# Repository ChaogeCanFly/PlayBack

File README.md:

# Augmented reality System - Playback
The study of bats requires the ability to record and generate sound waves in the ultrasonic ranges. The required bandwidth for such systems is up to 100kHz, which is much higher than the common acoustic systems designed for humans. Studying bat echolocation capabilities and generating real time acoustic responses requires a minimal latency acoustic system. The few available systems on the market aren`t designed for real time signal processing and manipulation. In order to meet those constrains, a full acoustic system was developed. The system includes a Smart microphone module embedded with a microprocessor, a Speaker-amplifier and a Switch box which is capable of signal redirection and real time processing.

## PlayBack
The PlayBack setup consists of three main modules: Smart Microphones, a Switch and speaker amplifiers.  It is designed to monitor audio signals from multiple microphone modules and direct a signal from a selected microphone to an array of speaker modules including DSP options for audio processing in real time. The setup is designed to work at an audio bandwidth of 1-100 kHz at up to 1MS/S.
 
 ### 3d Models:
The casings for the modules have been designed in Fusion 360 and 3d printed
[Microphone](https://a360.co/2HDuYLZ)
[Switch](https://a360.co/36yYfSj)
[Amplifier](https://a360.co/2WX1Lmh)

### System Diagram
The system’s topology is such that the microphone modules are connected to the switch module using a standard RJ25 cable. The 6 wires of the cable are used to pass the following between the Smart microphones and the Switch: power to the module, trigger signal, the audio signal and an analog “quality” signal. The Switch module consists of two MCU`s (Micro Controller Unit), one is used as the Switch interface, and routes the signals while the other is used as a DSP MCU to implement signal processing in real time to the acoustic signal. The speaker amplifiers are connected through an RJ45 cable which in turn is used to supply power from the switch to the amplifiers and transmit the audio signals and the enable signal to the amplifier. The Switch module is connected to a Matlab GUI application running on a PC using an Xbee adapter for wireless operation. In addition, a Saleae logic analyzer is connected to the Switch allowing to monitor the analog signals and the trigger signal.

### Smart Microphone
The Smart microphone module is designed to meet the required acoustic bandwidth of bat echolocation calls. In addition, since the system requirements are minimal latency for signal processing and signal manipulation, each of the microphones are embedded with a dedicated microprocessor which is responsible for the initial signal processing of the individual acoustic source. Such an approach allows spreading the computational power required by the system and simplifies the decision-making requirements of the Switch by reducing the acoustic information to a more simplified representation of an acoustic source. i.e. digital triggers / signal quality indication. This approach also allows future expending of the system since each of the microphones acts as an independent entity responsible for its own acoustic system. Adding more microphone to a system will not influence the required signal processing for the main unit.

### Switch
The Switch Module is used as the center piece of the system. It connects all the Smart microphone modules and Speaker amplifiers, has an analog routing circuitry to route one of the microphone signals to several speakers. In addition, it acts as a power delivery system, converting a single supply source to several voltage levels for the various components of the system. The switch contains several status indicators such as active speaker LEDs, external trigger. Connectors for all the analog signals running through the system and generally configured status LEDs for future configurations. The switch module contains two MCUs, Switch MCU and DSP MCU, the Switch MCU is used as the system interface and responsible for routing the acoustic signals and monitor the trigger events from the Smart Microphones, while the DSP MCU is used as a DSP and implements various signal processing algorithms.

### Speaker amplifier
Generating sounds in the ultrasonic frequencies (above 20kHz) requires a dedicated amplifier. Since commercial amplifiers are usually designed for the human hearing range and are commonly implemented through power efficient amplifiers (Class D). These speakers work as digital switches at high frequencies above the human hearing thresholds. The high frequency digital switching is converted to an analog signal using the natural low pass filtering characteristics of the speaker coils. The attempt to use such an amplifier at an ultrasonic frequency will result in high frequency distortions if any sound is generated at all since the common amplifiers are implemented with filters to cut the ultrasonic ranges from the input signals.

### GUI Microphone
To control the software parameters of the Smart Microphone, a GUI was created in Matlab. The Microphone has a UART communication over USB with the PC through the MCU`s micro USB connection or through an Xbee adapter board connected to its mate at the PC - as a wireless configuration. The GUI is designed with several section, Connection settings section, Parameters setting and display section, Messages section and Microphone updates section.

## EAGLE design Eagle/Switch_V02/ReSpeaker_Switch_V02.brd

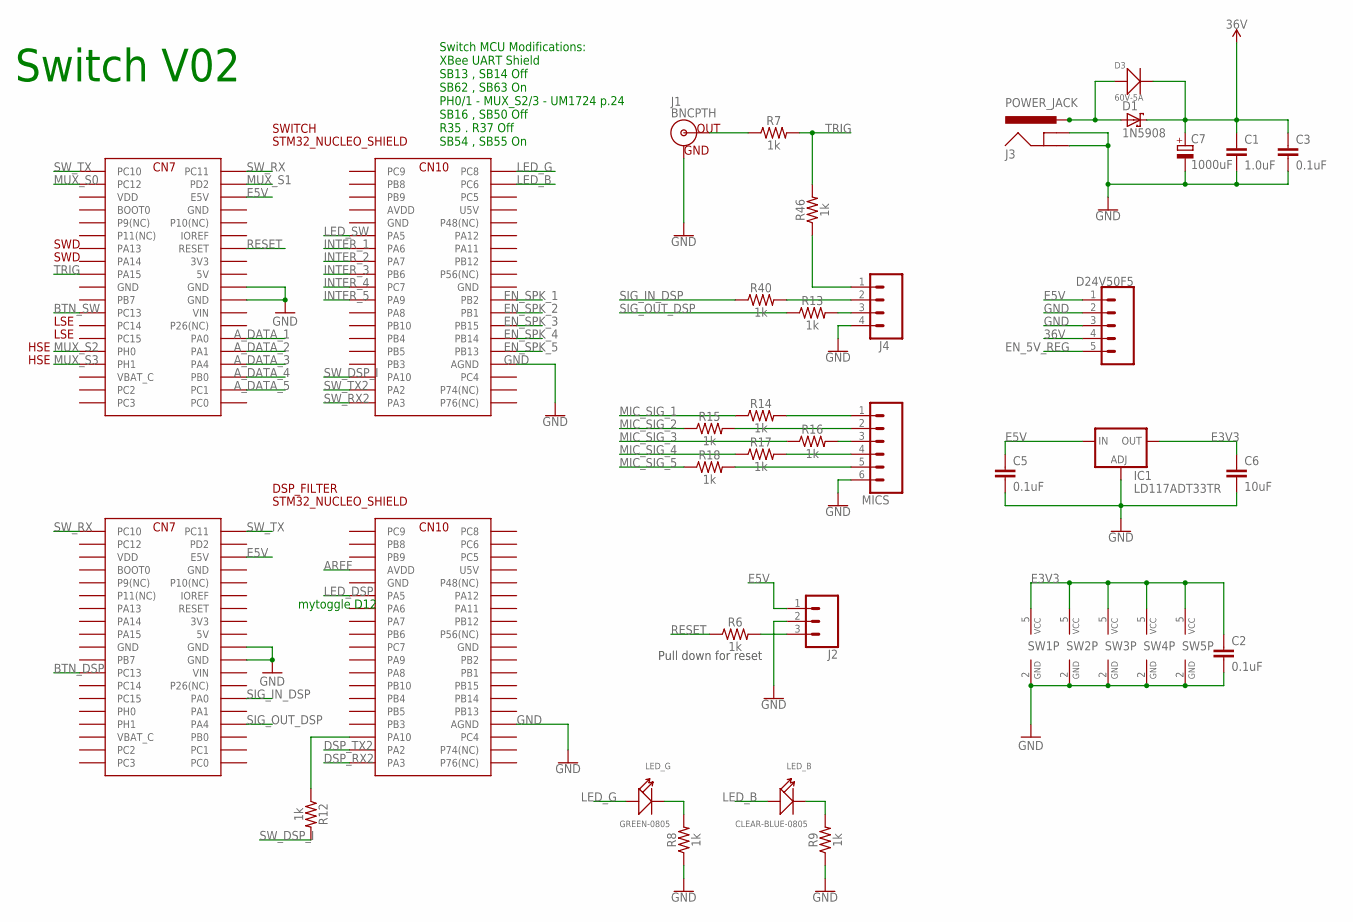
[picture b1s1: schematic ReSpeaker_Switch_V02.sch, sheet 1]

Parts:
C1: 1.0uF; 0805
C2, C3, C5: 0.1uF; 0805
C6: 10uF; 0805
C7: 1000uF; E7,5-16
D1: 1N5908; C4111-15
D3: 60V-5A; DO-214AB
D24V50F5: CONN_05; 1X05
DSP_FILTER: STM32_NUCLEO_SHIELD; STM32_NUCLEO
IC1: LD117ADT33TR; DPACK
J1: BNCPTH; BNC
J2: CONN_03POLAR; MOLEX-1X3
J3: POWER_JACK; POWER_JACK_PTH
J4: CONN_04POLAR; MOLEX-1X4
LED_B: CLEAR-BLUE-0805; LED-0805
LED_G: GREEN-0805; LED-0805
MICS: CONN_06POLAR; MOLEX-1X6
R6, R7, R8, R9, R12, R13, R14, R15, R16, R17, R18, R40, R46: 1k; 0805
SW1, SW2, SW3, SW4, SW5: 741G3157DBVR; DBV_R-PDSO-G6
SWITCH: STM32_NUCLEO_SHIELD; STM32_NUCLEO

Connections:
3V3: DSP_FILTER.3V3, SWITCH.3V3
5V: DSP_FILTER.5V, SWITCH.5V
36V: C1.1, C3.1, C7.+, D1.C, D3.2 (-), D24V50F5.4; also elsewhere on the board
AREF: DSP_FILTER.AVDD
AVDD: SWITCH.AVDD
A_DATA_1: SWITCH.PA0; also elsewhere on the board
A_DATA_2: SWITCH.PA1; also elsewhere on the board
A_DATA_3: SWITCH.PA4; also elsewhere on the board
A_DATA_4: SWITCH.PB0; also elsewhere on the board
A_DATA_5: SWITCH.PC1; also elsewhere on the board
BTN_DSP: DSP_FILTER.PC13
BTN_SW: SWITCH.PC13
DSP_RX2: DSP_FILTER.PA3
DSP_TX2: DSP_FILTER.PA2
E3V3: C2.1, C6.1, IC1.4 (OUT), SW1.5 (VCC), SW2.5 (VCC), SW3.5 (VCC), SW4.5 (VCC), SW5.5 (VCC); also elsewhere on the board
E5V: C5.1, D24V50F5.1, DSP_FILTER.E5V, IC1.3 (IN), J2.1, SWITCH.E5V; also elsewhere on the board
EN_5V_REG: D24V50F5.5
EN_SPK_1: SWITCH.PB2; also elsewhere on the board
EN_SPK_2: SWITCH.PB1; also elsewhere on the board
EN_SPK_3: SWITCH.PB15; also elsewhere on the board
EN_SPK_4: SWITCH.PB14; also elsewhere on the board
EN_SPK_5: SWITCH.PB13; also elsewhere on the board
GND: C1.2, C2.2, C3.2, C5.2, C6.2, C7.-, D24V50F5.2, D24V50F5.3, DSP_FILTER.AGND, DSP_FILTER.GND@8 (GND), DSP_FILTER.GND@19 (GND), DSP_FILTER.GND@20 (GND), DSP_FILTER.GND@22 (GND), DSP_FILTER.GND@47 (GND), DSP_FILTER.GND@58 (GND), IC1.1 (ADJ), J1.GND, J2.2, J3.GND, J3.GNDBREAK, J4.4, MICS.6, R8.1, R9.1, SW1.2 (GND), SW2.2 (GND), SW3.2 (GND), SW4.2 (GND), SW5.2 (GND), SWITCH.AGND, SWITCH.GND@8 (GND), SWITCH.GND@19 (GND), SWITCH.GND@20 (GND), SWITCH.GND@22 (GND), SWITCH.GND@47 (GND), SWITCH.GND@58 (GND); also elsewhere on the board
INTER_1: SWITCH.PA6; also elsewhere on the board
INTER_2: SWITCH.PA7; also elsewhere on the board
INTER_3: SWITCH.PB6; also elsewhere on the board
INTER_4: SWITCH.PC7; also elsewhere on the board
INTER_5: SWITCH.PA9; also elsewhere on the board
LED_B: LED_B.+, SWITCH.PC6
LED_DSP: DSP_FILTER.PA5
LED_G: LED_G.+, SWITCH.PC8
LED_SW: SWITCH.PA5
MIC_SIG_1: R14.1; also elsewhere on the board
MIC_SIG_2: R15.1; also elsewhere on the board
MIC_SIG_3: R16.1; also elsewhere on the board
MIC_SIG_4: R17.1; also elsewhere on the board
MIC_SIG_5: R18.1; also elsewhere on the board
MUX_S0: SWITCH.PC12; also elsewhere on the board
MUX_S1: SWITCH.PD2; also elsewhere on the board
MUX_S2: SWITCH.PH0; also elsewhere on the board
MUX_S3: SWITCH.PH1; also elsewhere on the board
unnamed: DSP_FILTER.PA10, R12.1
unnamed: D1.A, D3.1 (+), J3.PWR
unnamed: J1.S (OUT), R7.1
unnamed: J2.3, R6.2
unnamed: MICS.1, R14.2
unnamed: LED_G.-, R8.2
unnamed: LED_B.-, R9.2
unnamed: MICS.2, R15.2
unnamed: MICS.3, R16.2
unnamed: MICS.4, R17.2
unnamed: MICS.5, R18.2
unnamed: J4.2, R40.2
unnamed: J4.3, R13.2
unnamed: J4.1, R46.1
RESET: R6.1, SWITCH.RESET
SIG_IN_DSP: DSP_FILTER.PA0, R40.1; also elsewhere on the board
SIG_OUT_DSP: DSP_FILTER.PA4, R13.1; also elsewhere on the board
SW_DSP_I: R12.2, SWITCH.PA10
SW_RX: DSP_FILTER.PC10, SWITCH.PC11
SW_RX2: SWITCH.PA3
SW_TX: DSP_FILTER.PC11, SWITCH.PC10
SW_TX2: SWITCH.PA2
TRIG: R7.2, R46.2, SWITCH.PA15
U5V: DSP_FILTER.U5V, SWITCH.U5V
VBAT_C: DSP_FILTER.VBAT_C, SWITCH.VBAT_C
VDD: DSP_FILTER.VDD, SWITCH.VDD
VIN: DSP_FILTER.VIN, SWITCH.VIN

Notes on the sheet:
SWD
LSE
Switch V02
Pull down for reset
Switch MCU Modifications: XBee UART Shield SB13 , SB14 Off SB62 , SB63 On PH0/1 - MUX_S2/3 - UM1724 p.24 SB16 , SB50 Off R35 . R37 Off SB54 , SB55 On
HSE
mytoggle D12

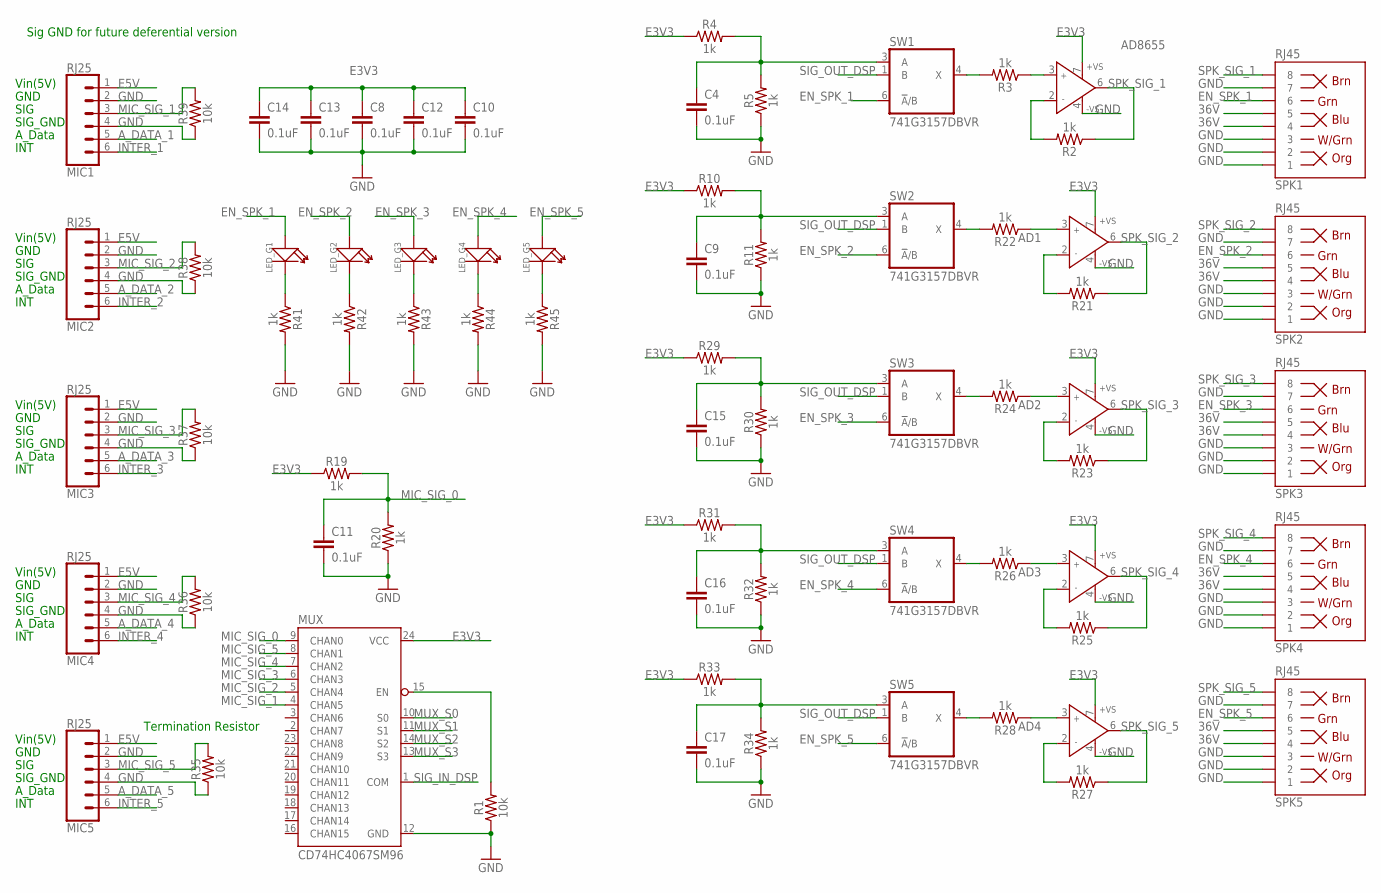
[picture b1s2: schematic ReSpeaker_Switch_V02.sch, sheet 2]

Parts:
AD1, AD2, AD3, AD4, AD8655: AD8655R; SO8
C4, C8, C9, C10, C11, C12, C13, C14, C15, C16, C17: 0.1uF; 0805
LED_G1, LED_G2, LED_G3, LED_G4, LED_G5: GREEN-0805; LED-0805
MIC1, MIC2, MIC3, MIC4, MIC5: RJ25; RJ11-6
MUX: CD74HC4067SM96; SSOP24
R1, R35, R36, R37, R38, R39: 10k; 0805
R2, R3, R4, R5, R10, R11, R19, R20, R21, R22, R23, R24, R25, R26, R27, R28, R29, R30, R31, R32, R33, R34, R41, R42, R43, R44, R45: 1k; 0805
SPK1, SPK2, SPK3, SPK4, SPK5: RJ45; RJ45-8
SW1, SW2, SW3, SW4, SW5: 741G3157DBVR; DBV_R-PDSO-G6

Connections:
36V: SPK1.4, SPK1.5, SPK2.4, SPK2.5, SPK3.4, SPK3.5, SPK4.4, SPK4.5, SPK5.4, SPK5.5; also elsewhere on the board
A_DATA_1: MIC1.5; also elsewhere on the board
A_DATA_2: MIC2.5; also elsewhere on the board
A_DATA_3: MIC3.5; also elsewhere on the board
A_DATA_4: MIC4.5; also elsewhere on the board
A_DATA_5: MIC5.5; also elsewhere on the board
E3V3: AD1.7 (+VS), AD2.7 (+VS), AD3.7 (+VS), AD4.7 (+VS), AD8655.7 (+VS), C8.1, C10.1, C12.1, C13.1, C14.1, MUX.24 (VCC), R4.1, R10.1, R19.1, R29.1, R31.1, R33.1; also elsewhere on the board
E5V: MIC1.1, MIC2.1, MIC3.1, MIC4.1, MIC5.1; also elsewhere on the board
EN_MUX: MUX.15 (EN), R1.2
EN_SPK_1: LED_G1.+, SPK1.6, SW1.6 (!A!/B); also elsewhere on the board
EN_SPK_2: LED_G2.+, SPK2.6, SW2.6 (!A!/B); also elsewhere on the board
EN_SPK_3: LED_G3.+, SPK3.6, SW3.6 (!A!/B); also elsewhere on the board
EN_SPK_4: LED_G4.+, SPK4.6, SW4.6 (!A!/B); also elsewhere on the board
EN_SPK_5: LED_G5.+, SPK5.6, SW5.6 (!A!/B); also elsewhere on the board
GND: AD1.4 (-VS), AD2.4 (-VS), AD3.4 (-VS), AD4.4 (-VS), AD8655.4 (-VS), C4.2, C8.2, C9.2, C10.2, C11.2, C12.2, C13.2, C14.2, C15.2, C16.2, C17.2, MIC1.2, MIC1.4, MIC2.2, MIC2.4, MIC3.2, MIC3.4, MIC4.2, MIC4.4, MIC5.2, MIC5.4, MUX.12 (GND), R1.1, R5.1, R11.1, R20.1, R30.1, R32.1, R34.1, R35.1, R36.1, R37.1, R38.1, R39.1, R41.2, R42.2, R43.2, R44.2, R45.2, SPK1.1, SPK1.2, SPK1.3, SPK1.7, SPK2.1, SPK2.2, SPK2.3, SPK2.7, SPK3.1, SPK3.2, SPK3.3, SPK3.7, SPK4.1, SPK4.2, SPK4.3, SPK4.7, SPK5.1, SPK5.2, SPK5.3, SPK5.7; also elsewhere on the board
INTER_1: MIC1.6; also elsewhere on the board
INTER_2: MIC2.6; also elsewhere on the board
INTER_3: MIC3.6; also elsewhere on the board
INTER_4: MIC4.6; also elsewhere on the board
INTER_5: MIC5.6; also elsewhere on the board
MIC_SIG_0: C11.1, MUX.9 (CHAN0), R19.2, R20.2
MIC_SIG_1: MIC1.3, MUX.4 (CHAN5), R39.2; also elsewhere on the board
MIC_SIG_2: MIC2.3, MUX.5 (CHAN4), R38.2; also elsewhere on the board
MIC_SIG_3: MIC3.3, MUX.6 (CHAN3), R37.2; also elsewhere on the board
MIC_SIG_4: MIC4.3, MUX.7 (CHAN2), R36.2; also elsewhere on the board
MIC_SIG_5: MIC5.3, MUX.8 (CHAN1), R35.2; also elsewhere on the board
MUX_S0: MUX.10 (S0); also elsewhere on the board
MUX_S1: MUX.11 (S1); also elsewhere on the board
MUX_S2: MUX.14 (S2); also elsewhere on the board
MUX_S3: MUX.13 (S3); also elsewhere on the board
unnamed: R3.2, SW1.4 (X)
unnamed: AD8655.3 (IN+), R3.1
unnamed: AD8655.2 (IN-), R2.2
unnamed: C4.1, R4.2, R5.2, SW1.3 (A)
unnamed: C9.1, R10.2, R11.2, SW2.3 (A)
unnamed: AD1.2 (IN-), R21.2
unnamed: AD2.2 (IN-), R23.2
unnamed: AD1.3 (IN+), R22.1
unnamed: AD2.3 (IN+), R24.1
unnamed: AD3.2 (IN-), R25.2
unnamed: AD3.3 (IN+), R26.1
unnamed: AD4.2 (IN-), R27.2
unnamed: AD4.3 (IN+), R28.1
unnamed: C15.1, R29.2, R30.2, SW3.3 (A)
unnamed: R22.2, SW2.4 (X)
unnamed: C16.1, R31.2, R32.2, SW4.3 (A)
unnamed: R24.2, SW3.4 (X)
unnamed: C17.1, R33.2, R34.2, SW5.3 (A)
unnamed: R26.2, SW4.4 (X)
unnamed: R28.2, SW5.4 (X)
unnamed: LED_G1.-, R41.1
unnamed: LED_G2.-, R42.1
unnamed: LED_G3.-, R43.1
unnamed: LED_G4.-, R44.1
unnamed: LED_G5.-, R45.1
SIG_IN_DSP: MUX.1 (COM); also elsewhere on the board
SIG_OUT_DSP: SW1.1 (B), SW2.1 (B), SW3.1 (B), SW4.1 (B), SW5.1 (B); also elsewhere on the board
SPK_SIG_1: AD8655.6 (OUT), R2.1, SPK1.8
SPK_SIG_2: AD1.6 (OUT), R21.1, SPK2.8
SPK_SIG_3: AD2.6 (OUT), R23.1, SPK3.8
SPK_SIG_4: AD3.6 (OUT), R25.1, SPK4.8
SPK_SIG_5: AD4.6 (OUT), R27.1, SPK5.8

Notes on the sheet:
SIG
SIG_GND
Vin(5V)
GND
A_Data
INT
Sig GND for future deferential version
Termination Resistor

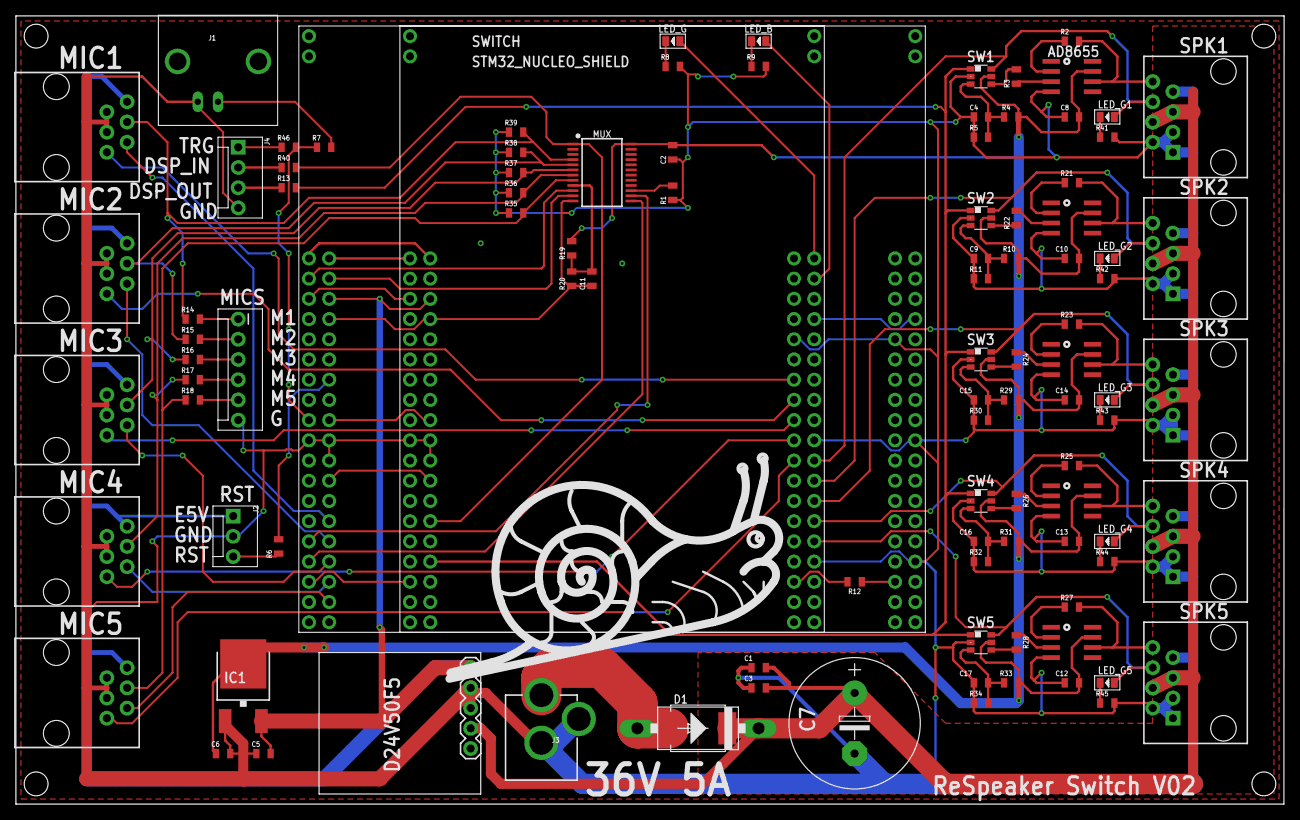
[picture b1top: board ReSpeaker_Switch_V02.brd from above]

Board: 2 copper layers, 159.4 x 99.1 mm, 102 parts (0 on the bottom side), 89 nets.

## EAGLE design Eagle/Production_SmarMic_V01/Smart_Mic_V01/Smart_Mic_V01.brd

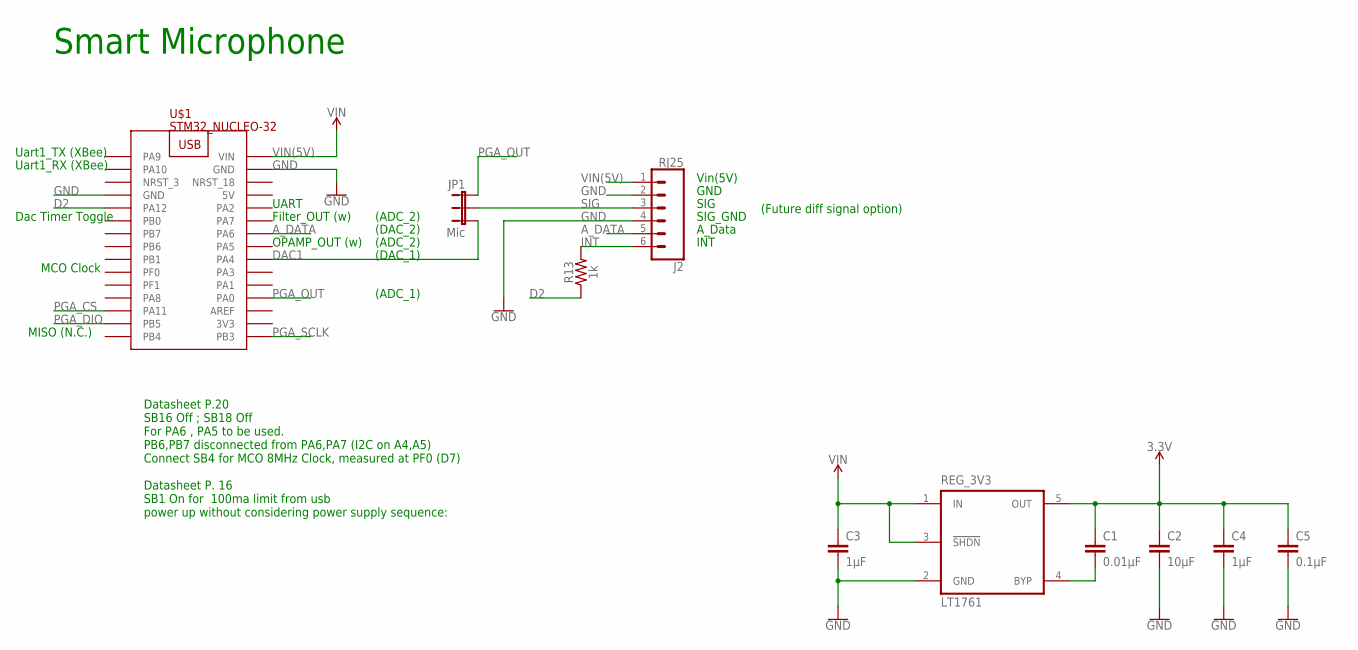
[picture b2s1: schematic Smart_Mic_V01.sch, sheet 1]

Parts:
C1: 0.01µF; 0805
C2: 10µF; 0805
C3, C4: 1µF; 0805
C5: 0.1µF; 0805
J2: RJ25; RJ11-6
JP1: Mic; 1X03
R13: 1k; 0805
REG_3V3: LT1761; SOT23-5
U$1: STM32_NUCLEO-32

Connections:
3.3V: C1.1, C2.1, C4.1, C5.1, REG_3V3.5 (OUT); also elsewhere on the board
3V3: U$1.3V3
5V: U$1.5V
A_DATA: J2.5, U$1.PA6
BYP: C1.2, REG_3V3.4 (BYP)
D2: R13.1, U$1.PA12
DAC1: JP1.3, U$1.PA4
GND: C2.2, C3.2, C4.2, C5.2, J2.2, J2.4, REG_3V3.2 (GND), U$1.GND@4 (GND), U$1.GND@17 (GND); also elsewhere on the board
INT: J2.6, R13.2
PGA_CS: U$1.PA11; also elsewhere on the board
PGA_DIO: U$1.PB5; also elsewhere on the board
PGA_OUT: JP1.1, U$1.PA0; also elsewhere on the board
PGA_SCLK: U$1.PB3; also elsewhere on the board
SIG: J2.3, JP1.2
VIN(5V): C3.1, J2.1, REG_3V3.1 (IN), REG_3V3.3 (!SHDN!), U$1.VIN

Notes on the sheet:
Smart Microphone
SIG
SIG_GND
Vin(5V)
GND
A_Data
INT
(Future diff signal option)
(ADC_1)
(ADC_2)
(DAC_1)
(DAC_2)
UART
Datasheet P.20 SB16 Off ; SB18 Off For PA6 , PA5 to be used. PB6,PB7 disconnected from PA6,PA7 (I2C on A4,A5) Connect SB4 for MCO 8MHz Clock, measured at PF0 (D7) Datasheet P. 16 SB1 On for 100ma limit from usb power up without considering power supply sequence:
MISO (N.C.)
OPAMP_OUT (w)
Filter_OUT (w)
Uart1_TX (XBee)
Uart1_RX (XBee)
MCO Clock
Dac Timer Toggle

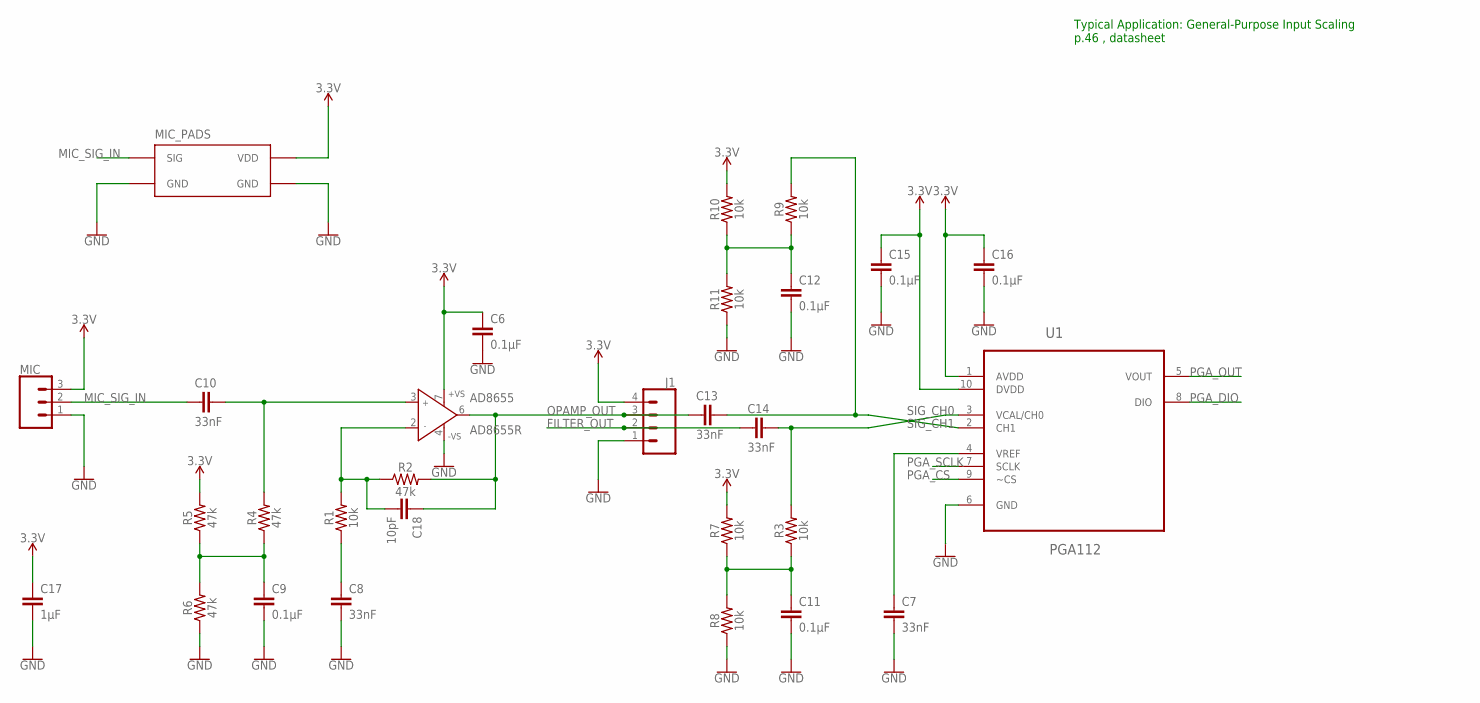
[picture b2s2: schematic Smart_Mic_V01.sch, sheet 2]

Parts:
AD8655: AD8655R; SO8
C6, C9, C11, C12, C15, C16: 0.1µF; 0805
C7, C8, C10, C13, C14: 33nF; 0805
C17: 1µF; 0805
C18: 10pF; 0805
J1: CONN_04; 1X04
MIC: CONN_03; 1X03
R1, R3, R7, R8, R9, R10, R11: 10k; 0805
R2, R4, R5, R6: 47k; 0805
U1: PGA112; SOP50P490X110-10N
U$2: MIC_PADS

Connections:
3.3V: AD8655.7 (+VS), C6.1, C15.1, C16.1, C17.1, J1.4, MIC.3, R5.2, R7.2, R10.2, U1.1 (AVDD), U1.10 (DVDD), U$2.VDD; also elsewhere on the board
FILTER_OUT: C14.2, J1.2
GND: AD8655.4 (-VS), C6.2, C7.2, C8.2, C9.2, C11.2, C12.2, C15.2, C16.2, C17.2, J1.1, MIC.1, R6.1, R8.1, R11.1, U1.6 (GND), U$2.GND$2 (GND), U$2.GND$4 (GND); also elsewhere on the board
MIC_SIG_IN: C10.2, MIC.2, U$2.SIG
unnamed: C7.1, U1.4 (VREF)
unnamed: C9.1, R4.1, R5.1, R6.2
unnamed: C11.1, R3.1, R7.1, R8.2
unnamed: C12.1, R9.1, R10.1, R11.2
unnamed: C8.1, R1.1
OP1_+: AD8655.3 (IN+), C10.1, R4.2
OP1_-: AD8655.2 (IN-), C18.2, R1.2, R2.1
OPAMP_OUT: AD8655.6 (OUT), C13.2, C18.1, J1.3, R2.2
PGA_CS: U1.9 (~CS); also elsewhere on the board
PGA_DIO: U1.8 (DIO); also elsewhere on the board
PGA_OUT: U1.5 (VOUT); also elsewhere on the board
PGA_SCLK: U1.7 (SCLK); also elsewhere on the board
SIG_CH0: C13.1, R9.2, U1.2 (CH1)
SIG_CH1: C14.1, R3.2, U1.3 (VCAL/CH0)

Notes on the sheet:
Typical Application: General-Purpose Input Scaling p.46 , datasheet

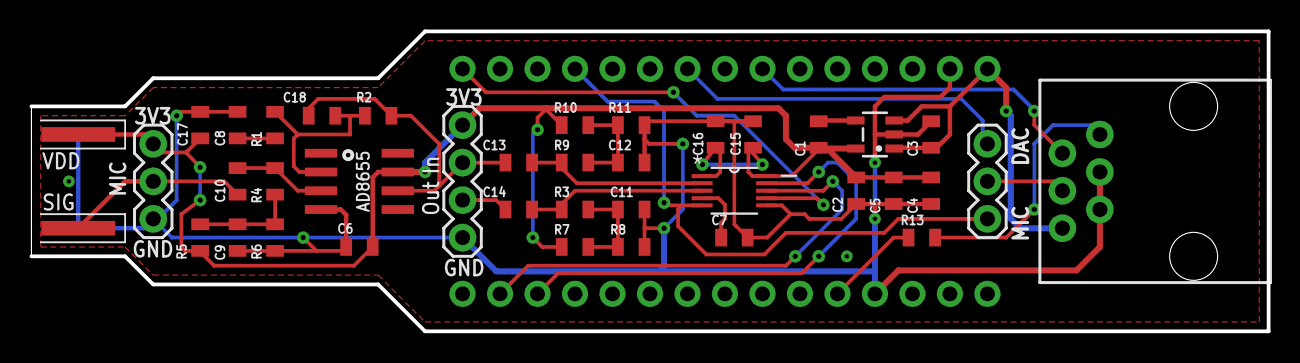
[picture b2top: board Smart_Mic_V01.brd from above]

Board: 2 copper layers, 83.8 x 20.3 mm, 39 parts (1 on the bottom side), 25 nets.

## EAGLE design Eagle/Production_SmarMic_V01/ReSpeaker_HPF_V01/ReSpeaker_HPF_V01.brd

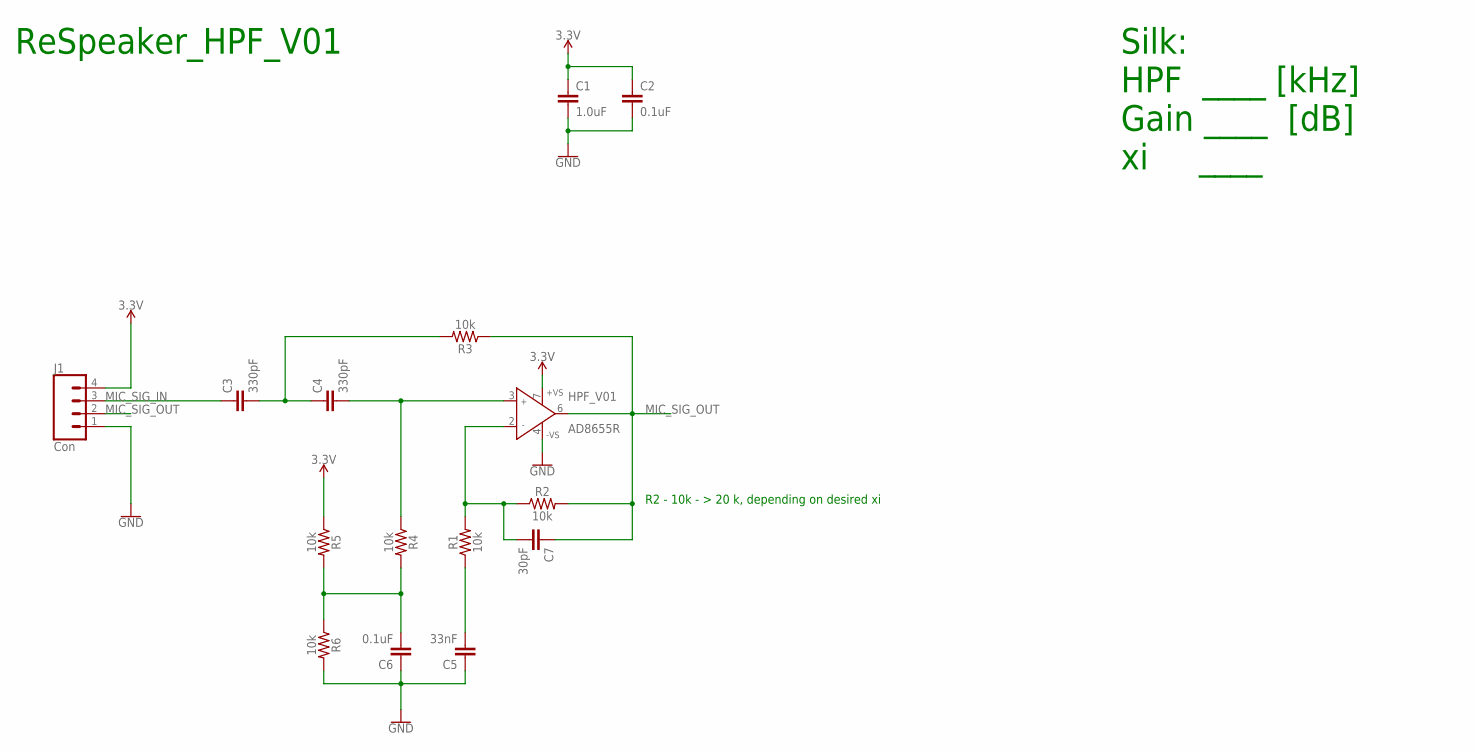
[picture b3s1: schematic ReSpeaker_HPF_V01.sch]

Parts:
C1: 1.0uF; 0805
C2, C6: 0.1uF; 0805
C3, C4: 330pF; 0805
C5: 33nF; 0805
C7: 30pF; 0805
HPF_V01: AD8655R; SO8
J1: Con; 1X04
R1, R2, R3, R4, R5, R6: 10k; 0805

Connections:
3.3V: C1.1, C2.1, HPF_V01.7 (+VS), J1.4, R5.1
GND: C1.2, C2.2, C5.1, C6.1, HPF_V01.4 (-VS), J1.1, R6.2
MIC_SIG_IN: C3.1, J1.3
MIC_SIG_OUT: C7.1, HPF_V01.6 (OUT), J1.2, R2.2, R3.1
unnamed: C3.2, C4.1, R3.2
unnamed: C4.2, HPF_V01.3 (IN+), R4.1
unnamed: C7.2, HPF_V01.2 (IN-), R1.2, R2.1
unnamed: C5.2, R1.1
unnamed: C6.2, R4.2, R5.2, R6.1

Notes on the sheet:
ReSpeaker_HPF_V01
R2 - 10k - > 20 k, depending on desired xi
Silk: HPF ____ [kHz] Gain ____ [dB] xi ____

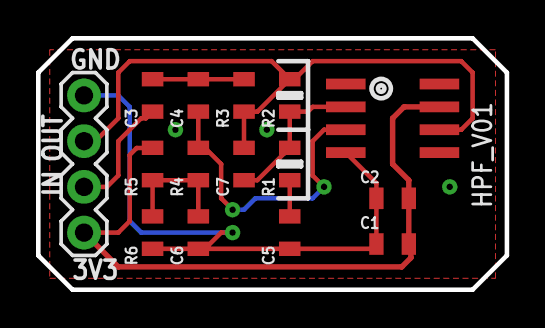
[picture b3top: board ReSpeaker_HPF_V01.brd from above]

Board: 2 copper layers, 26.0 x 14.0 mm, 15 parts (0 on the bottom side), 9 nets.

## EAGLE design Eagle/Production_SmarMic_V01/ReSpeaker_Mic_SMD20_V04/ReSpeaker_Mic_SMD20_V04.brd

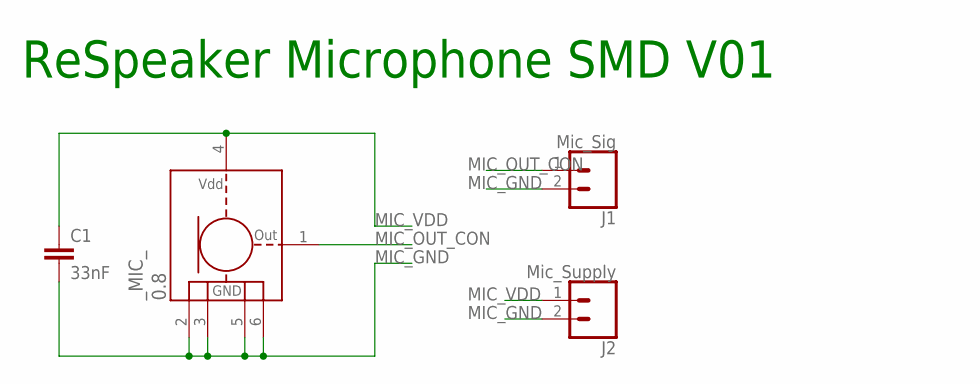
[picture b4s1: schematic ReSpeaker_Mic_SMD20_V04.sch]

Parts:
C1: 33nF; 0805
J1: Mic_Sig; 1X02_2.0MM
J2: Mic_Supply; 1X02_2.0MM
_MIC_: 0.8; SPU0410LR5H-QB_0.8

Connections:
MIC_GND: C1.2, J1.2, J2.2, _MIC_.2 (GND), _MIC_.3 (GND), _MIC_.5 (GND), _MIC_.6 (GND)
MIC_OUT_CON: J1.1, _MIC_.1 (OUT)
MIC_VDD: C1.1, J2.1, _MIC_.4 (VDD)

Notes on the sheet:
ReSpeaker Microphone SMD V01

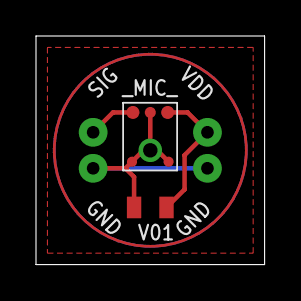
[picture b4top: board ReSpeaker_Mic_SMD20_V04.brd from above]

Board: 2 copper layers, 12.7 x 12.7 mm, 4 parts (0 on the bottom side), 3 nets.

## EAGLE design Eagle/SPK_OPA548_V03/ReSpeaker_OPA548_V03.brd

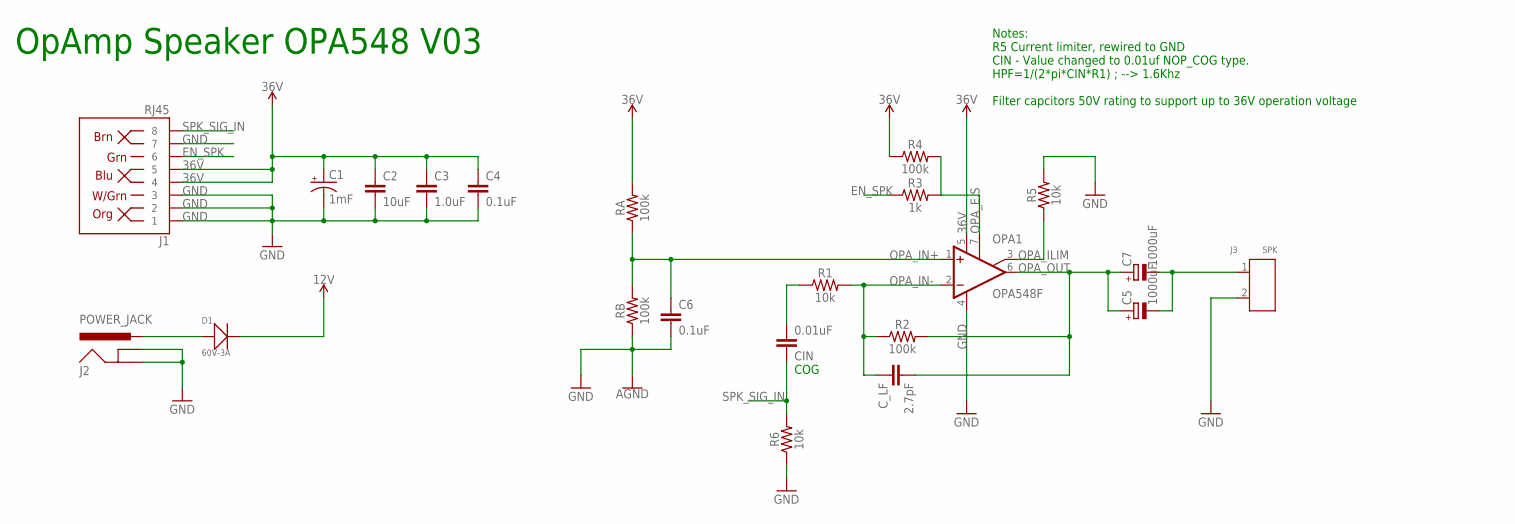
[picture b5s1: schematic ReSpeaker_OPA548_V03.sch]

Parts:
C1: 1mF; CPOL-RADIAL-5MM-10MM
C2: 10uF; 0805
C3: 1.0uF; 0805
C4, C6: 0.1uF; 0805
C5, C7: 1000uF; E7,5-16
CIN: 0.01uF; 0805
C_LF: 2.7pF; 0805
D1: 60V-3A; DO-214AB
J1: RJ45; RJ45-8
J2: POWER_JACK; POWER_JACK_PTH
J3: SPK; H2-5.0-10.5X8.0MM
OPA1: OPA548F; DD-7
R1, R5, R6: 10k; 0805
R2, R4: 100k; 0805
R3: 1k; 0805
RA: 100k; 0805
RB: 100k; 0805

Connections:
36V: C1.+, C2.1, C3.1, C4.1, D1.2 (-), J1.4, J1.5, OPA1.5 (V+), R4.1, RA.2
EN_SPK: J1.6, R3.1
GND: C1.-, C2.2, C3.2, C4.2, C6.2, J1.1, J1.2, J1.3, J1.7, J2.GND, J2.GNDBREAK, J3.2, OPA1.4 (V-), R5.2, R6.1, RB.1
unnamed: D1.1 (+), J2.PWR
unnamed: C5.-, C7.-, J3.1
unnamed: CIN.2, R1.1
OPA_E.S: OPA1.7 (E/S), R3.2, R4.2
OPA_ILIM: OPA1.3 (ILIM), R5.1
OPA_IN+: C6.1, OPA1.1 (+IN), RA.1, RB.2
OPA_IN-: C_LF.1, OPA1.2 (-IN), R1.2, R2.1
OPA_OUT: C5.+, C7.+, C_LF.2, OPA1.6 (OUT), R2.2
SPK_SIG_IN: CIN.1, J1.8, R6.2

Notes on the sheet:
Notes: R5 Current limiter, rewired to GND CIN - Value changed to 0.01uf NOP_COG type. HPF=1/(2*pi*CIN*R1) ; --> 1.6Khz Filter capcitors 50V rating to support up to 36V operation voltage
COG
OpAmp Speaker OPA548 V03

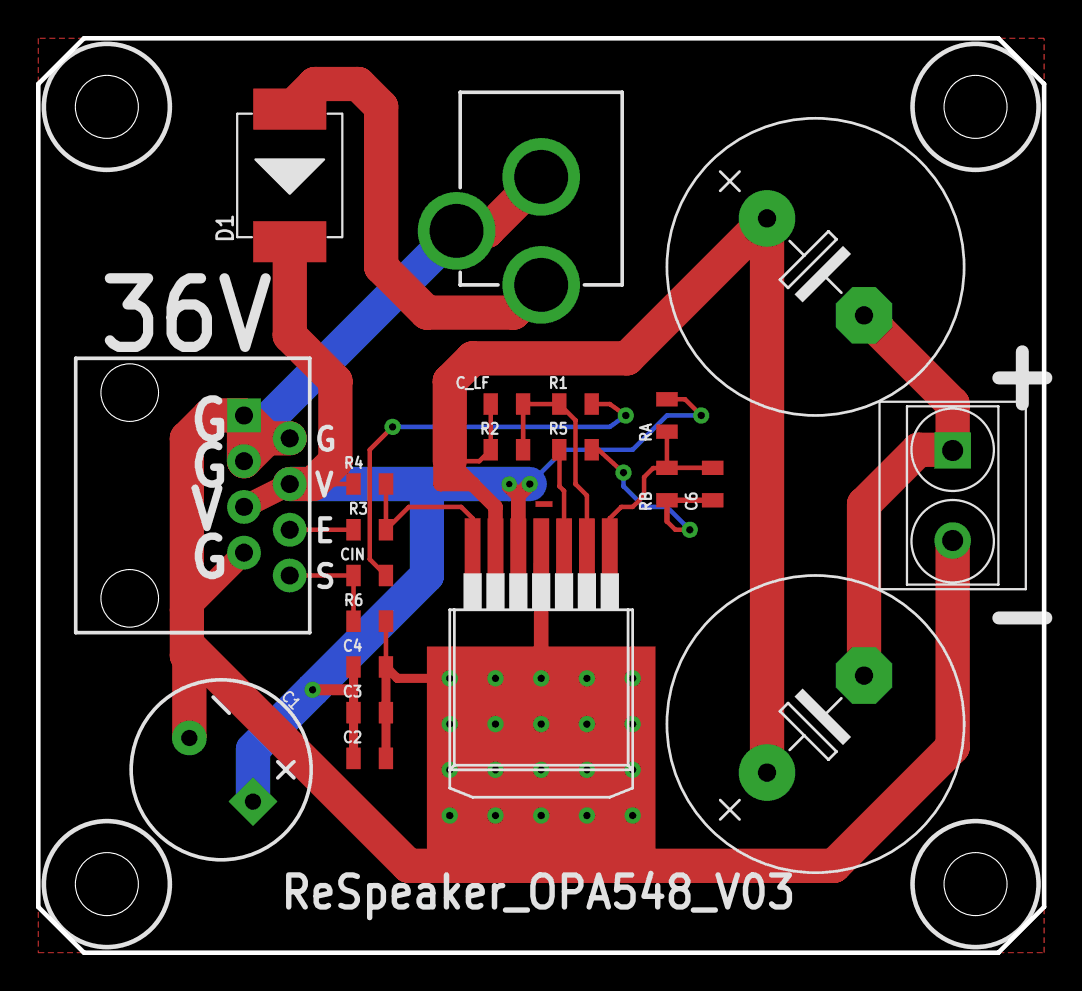
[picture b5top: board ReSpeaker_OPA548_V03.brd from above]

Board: 2 copper layers, 55.9 x 50.8 mm, 22 parts (0 on the bottom side), 12 nets.

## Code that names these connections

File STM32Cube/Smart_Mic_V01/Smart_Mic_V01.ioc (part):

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Mcu.Name=STM32F303K(6-8)Tx
Mcu.Package=LQFP32
Mcu.UserName=STM32F303K8Tx
PA0.GPIOParameters=GPIO_Label
PA0.GPIO_Label=PGA_OUT
PA0.Mode=IN1-Single-Ended
PA0.Signal=ADC1_IN1
PA10.GPIOParameters=GPIO_Label
PA10.GPIO_Label=XBEE_RX
PA10.Mode=Asynchronous
PA10.Signal=USART1_RX
PA11.GPIOParameters=GPIO_Speed,GPIO_Label
PA11.GPIO_Label=PGA_CS
PA11.GPIO_Speed=GPIO_SPEED_FREQ_HIGH
PA11.Signal=GPIO_Output
PA12.GPIOParameters=GPIO_Label
PA12.GPIO_Label=D2_INT
PA12.Signal=GPIO_Output
PA13.GPIOParameters=GPIO_Label
PA13.GPIO_Label=SWDIO
PA13.Mode=Serial_Wire
PA13.Signal=SYS_JTMS-SWDIO
PA14.GPIOParameters=GPIO_Label
PA14.GPIO_Label=SWCLK
PA14.Mode=Serial_Wire
PA14.Signal=SYS_JTCK-SWCLK
PA15.GPIOParameters=GPIO_Label
PA15.GPIO_Label=VCP_RX
PA15.Mode=Asynchronous
PA15.Signal=USART2_RX
PA2.GPIOParameters=GPIO_Label
PA2.GPIO_Label=VCP_TX
PA2.Mode=Asynchronous
PA2.Signal=USART2_TX
PA4.GPIOParameters=GPIO_Label
PA4.GPIO_Label=MIC_OUT
PA4.Signal=COMP_DAC11_group
PA6.GPIOParameters=GPIO_Label
PA6.GPIO_Label=A_DATA
PA6.Signal=COMP_DAC21_group
PA9.GPIOParameters=GPIO_Label
PA9.GPIO_Label=XBEE_TX
PA9.Mode=Asynchronous
PA9.Signal=USART1_TX
PB3.GPIOParameters=GPIO_Label
PB3.GPIO_Label=PGA_SCK
PB3.Mode=TX_Only_Simplex_Unidirect_Master
PB3.Signal=SPI1_SCK
PB5.GPIOParameters=GPIO_Label
PB5.GPIO_Label=PGA_MOSI
PB5.Mode=TX_Only_Simplex_Unidirect_Master
PB5.Signal=SPI1_MOSI
PF0\ /\ OSC_IN.GPIOParameters=GPIO_Label
PF0\ /\ OSC_IN.GPIO_Label=MCO
PF0\ /\ OSC_IN.Mode=HSE-External-Clock-Source
PF0\ /\ OSC_IN.Signal=RCC_OSC_IN
RCC.HSEPLLFreq_Value=8000000
RCC.HSE_VALUE=8000000
RCC.SYSCLKFreq_VALUE=72000000
RCC.SYSCLKSourceVirtual=RCC_SYSCLKSOURCE_PLLCLK
board=NUCLEO-F303K8
boardIOC=true

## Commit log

2020-05-25 added images
2020-07-22 changed file name

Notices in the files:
parts and their libraries:
SparkFun-Capacitors: Licensing: Creative Commons ShareAlike 4.0 International - https://creativecommons.org/licenses/by-sa/4.0
